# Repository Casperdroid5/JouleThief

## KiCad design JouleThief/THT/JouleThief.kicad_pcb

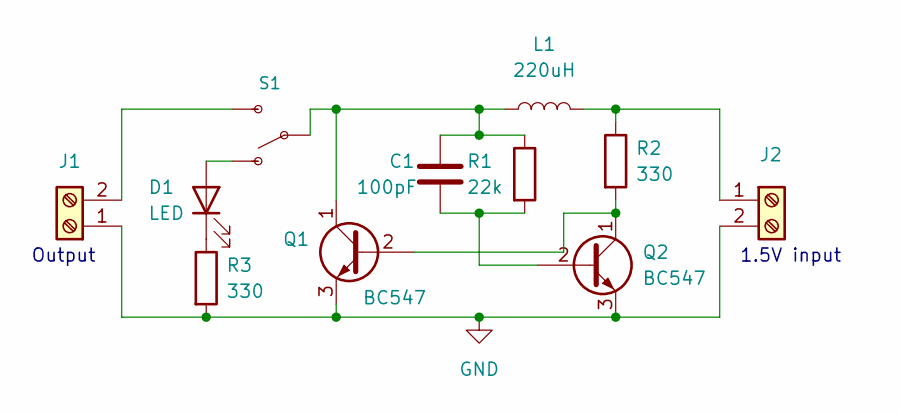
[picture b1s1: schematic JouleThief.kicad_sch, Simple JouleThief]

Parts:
C1: 100pF; C_Axial_L5.1mm_D3.1mm_P7.50mm_Horizontal
D1: LED; LED_D5.0mm_Clear
J1, J2: Screw_Terminal_01x02; TerminalBlock_bornier-2_P5.08mm
L1: 220uH; L_Axial_L5.0mm_D3.6mm_P10.00mm_Horizontal_Murata_BL01RN1A2A2
Q1, Q2: BC547; TO-92_Inline
R1: 22k; R_Axial_DIN0204_L3.6mm_D1.6mm_P7.62mm_Horizontal
R2, R3: 330; R_Axial_DIN0204_L3.6mm_D1.6mm_P7.62mm_Horizontal
S1: SWITCH-SPDT-PTH-11.6X4.0MM-KIT; SW_1825159-1

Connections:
GND: J1.1, J2.2, Q1.3 (E), Q2.3 (E), R3.2
unnamed: C1.1, L1.1, Q1.1 (C), R1.1, S1.2
unnamed: C1.2, Q2.2 (B), R1.2
unnamed: D1.1 (K), R3.1
unnamed: D1.2 (A), S1.1 (O)
unnamed: J1.2, S1.3 (S)
unnamed: J2.1, L1.2, R2.1
unnamed: Q1.2 (B), Q2.1 (C), R2.2

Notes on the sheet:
Output
1.5V input

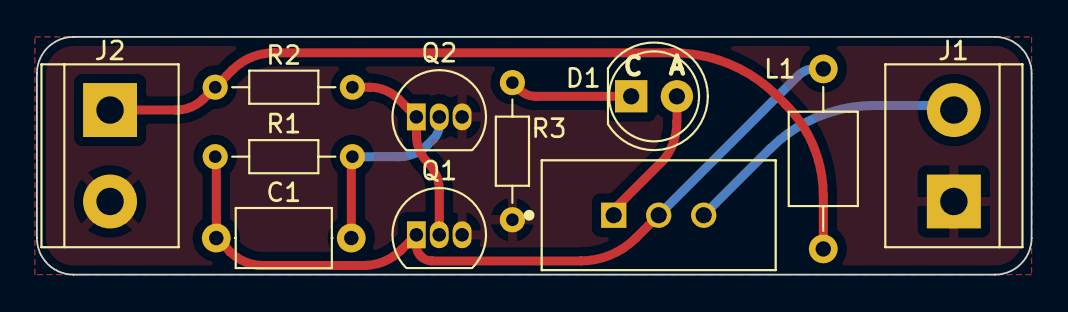
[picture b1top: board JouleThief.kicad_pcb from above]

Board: 2 copper layers, 55.3 x 13.2 mm, 11 parts (0 on the bottom side), 8 nets.

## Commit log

2022-10-08 schematic finished
2022-10-08 Finished PCB
2022-10-08 silkscreen enh
2022-10-08 enh silkscreen
2022-10-08 added fabrication files and cleanup
2022-10-08 smd parts found and added.
2022-10-08 Finished SMD JouleThief functional
    added silkscreen
2022-10-08 production and smooth traces add
2022-10-08 rem zip files
2022-10-08 rem backups
2022-10-09 Created SMD and THT boards
2022-11-08 Updated Joule thief schematic values
    Inductor: 220uH
    Capacitor: 100pF
2022-11-08 added working of the circuit pdf
2022-11-21 added tht components back tot tht
